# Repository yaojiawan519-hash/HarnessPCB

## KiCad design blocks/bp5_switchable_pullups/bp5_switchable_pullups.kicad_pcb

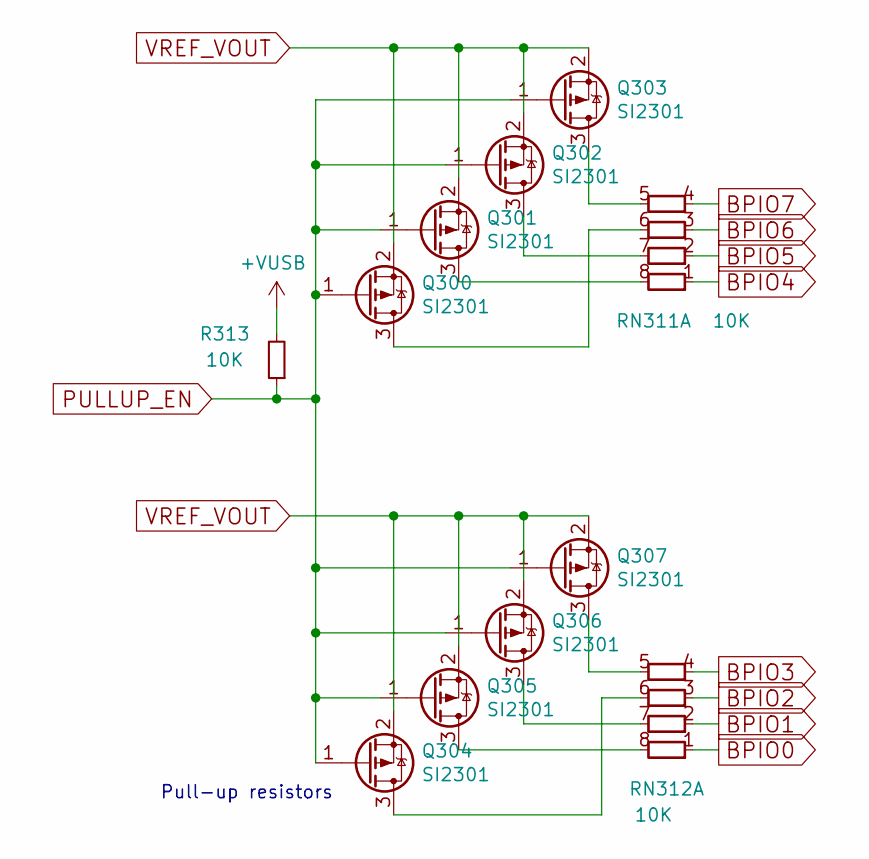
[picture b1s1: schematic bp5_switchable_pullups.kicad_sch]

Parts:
Q300, Q301, Q302, Q303, Q304, Q305, Q306, Q307: SI2301; SOT-523
R313: 10K; R_0402_1005Metric
RN311, RN312: 10K; R_Array_Convex_4x0402

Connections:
+VUSB: R313.2
BPIO0: RN312.1 (R1.1)
BPIO1: RN312.2 (R1.1)
BPIO2: RN312.3 (R1.1)
BPIO3: RN312.4 (R1.1)
BPIO4: RN311.1 (R1.1)
BPIO5: RN311.2 (R1.1)
BPIO6: RN311.3 (R1.1)
BPIO7: RN311.4 (R1.1)
unnamed: Q300.3 (D), RN311.6 (R1.8)
unnamed: Q301.3 (D), RN311.8 (R1.8)
unnamed: Q302.3 (D), RN311.7 (R1.8)
unnamed: Q303.3 (D), RN311.5 (R1.8)
unnamed: Q304.3 (D), RN312.6 (R1.8)
unnamed: Q305.3 (D), RN312.8 (R1.8)
unnamed: Q306.3 (D), RN312.7 (R1.8)
unnamed: Q307.3 (D), RN312.5 (R1.8)
PULLUP_EN: Q300.1 (G), Q301.1 (G), Q302.1 (G), Q303.1 (G), Q304.1 (G), Q305.1 (G), Q306.1 (G), Q307.1 (G), R313.1
VREF_VOUT: Q300.2 (S), Q301.2 (S), Q302.2 (S), Q303.2 (S), Q304.2 (S), Q305.2 (S), Q306.2 (S), Q307.2 (S)

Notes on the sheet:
Pull-up resistors

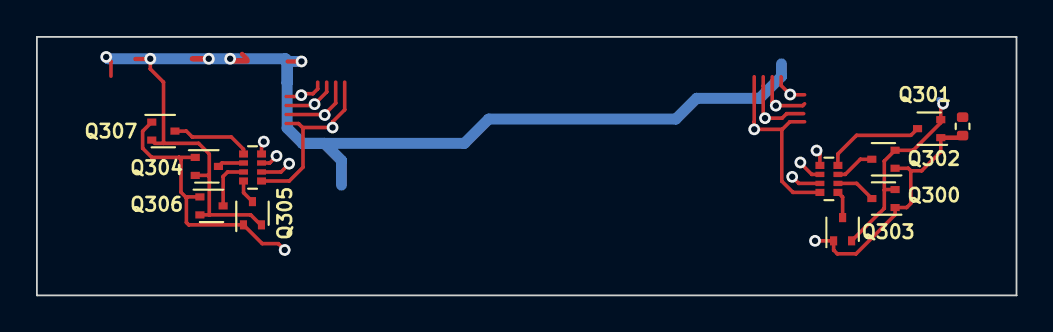
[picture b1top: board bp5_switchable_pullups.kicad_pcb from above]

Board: 4 copper layers, 54.4 x 14.4 mm, 11 parts (0 on the bottom side), 10 nets.

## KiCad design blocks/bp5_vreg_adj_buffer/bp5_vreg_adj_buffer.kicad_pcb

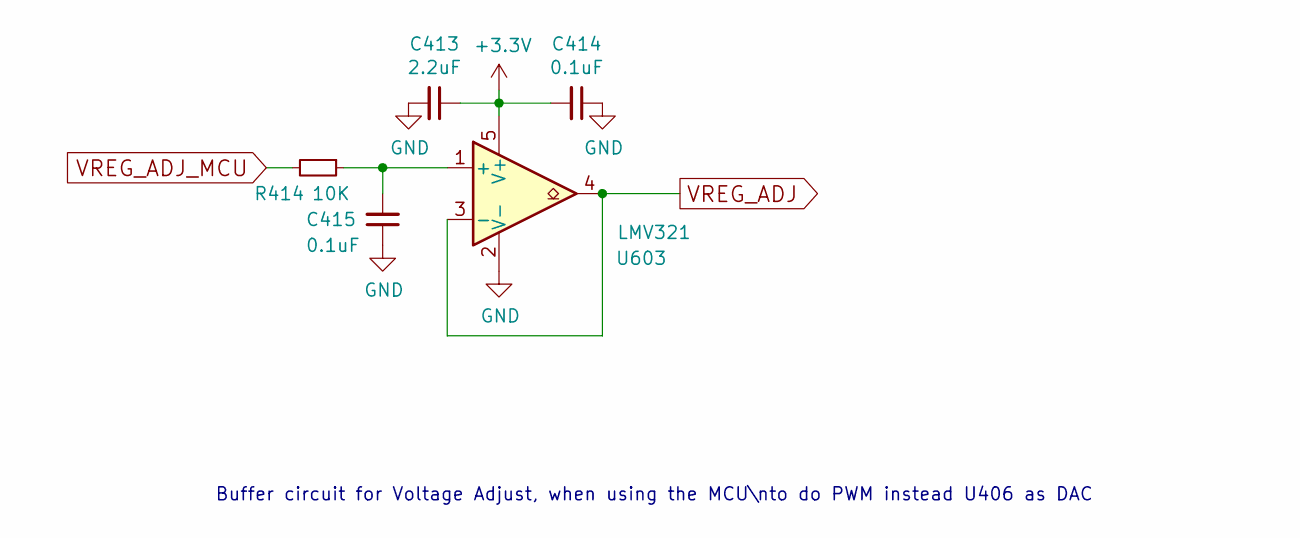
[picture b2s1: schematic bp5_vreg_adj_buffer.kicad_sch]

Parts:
C413: 2.2uF; C_0402_1005Metric
C414, C415: 0.1uF; C_0402_1005Metric
R414: 10K; R_0402_1005Metric
U603: LMV321; SOT-23-5

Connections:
+3V3: C413.1, C414.2, U603.5 (V+)
GND: C413.2, C414.1, C415.1, U603.2 (V-)
unnamed: C415.2, R414.1, U603.1 (+)
VREG_ADJ: U603.3 (-), U603.4
VREG_ADJ_MCU: R414.2

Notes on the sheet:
Buffer circuit for Voltage Adjust, when using the MCU\nto do PWM instead U406 as DAC

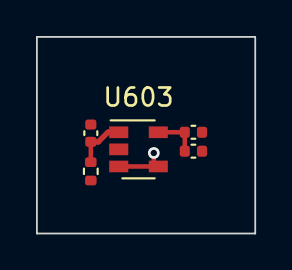
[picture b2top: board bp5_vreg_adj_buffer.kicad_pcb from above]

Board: 4 copper layers, 12.1 x 10.9 mm, 5 parts (0 on the bottom side), 4 nets.

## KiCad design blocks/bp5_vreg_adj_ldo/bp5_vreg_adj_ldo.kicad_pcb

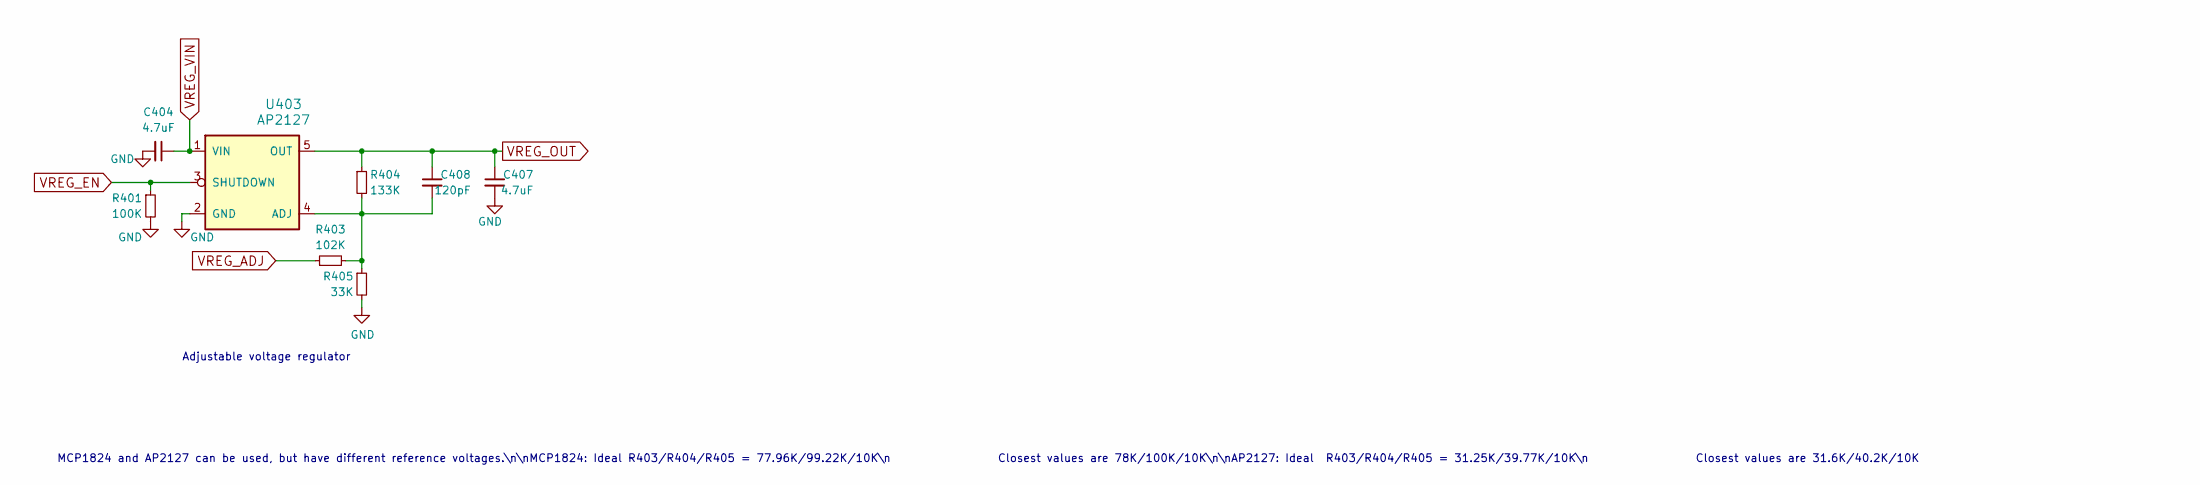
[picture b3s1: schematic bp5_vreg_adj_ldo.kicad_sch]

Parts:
C404, C407: 4.7uF; C_0402_1005Metric
C408: 120pF; C_0402_1005Metric
R401: 100K; R_0402_1005Metric
R403: 102K; R_0402_1005Metric
R404: 133K; R_0402_1005Metric
R405: 33K; R_0402_1005Metric
U403: AP2127; SOT-23-5

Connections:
GND: C404.2, C407.2, R401.2, R405.2, U403.2 (GND)
unnamed: C408.2, R403.2, R404.2, R405.1, U403.4 (ADJ)
VREG_ADJ: R403.1
VREG_EN: R401.1, U403.3 (SHUTDOWN)
VREG_OUT: C407.1, C408.1, R404.1, U403.5 (OUT)
VREG_VIN: C404.1, U403.1 (VIN)

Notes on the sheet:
Adjustable voltage regulator
MCP1824 and AP2127 can be used, but have different reference voltages.\n\nMCP1824: Ideal R403/R404/R405 = 77.96K/99.22K/10K\n Closest values are 78K/100K/10K\n\nAP2127: Ideal R403/R404/R405 = 31.25K/39.77K/10K\n Closest values are 31.6K/40.2K/10K

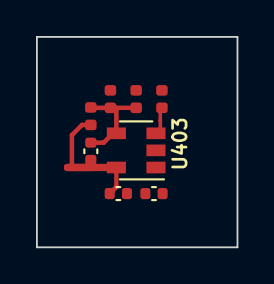
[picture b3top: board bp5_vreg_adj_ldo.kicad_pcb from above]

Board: 4 copper layers, 11.1 x 11.7 mm, 8 parts (0 on the bottom side), 5 nets.

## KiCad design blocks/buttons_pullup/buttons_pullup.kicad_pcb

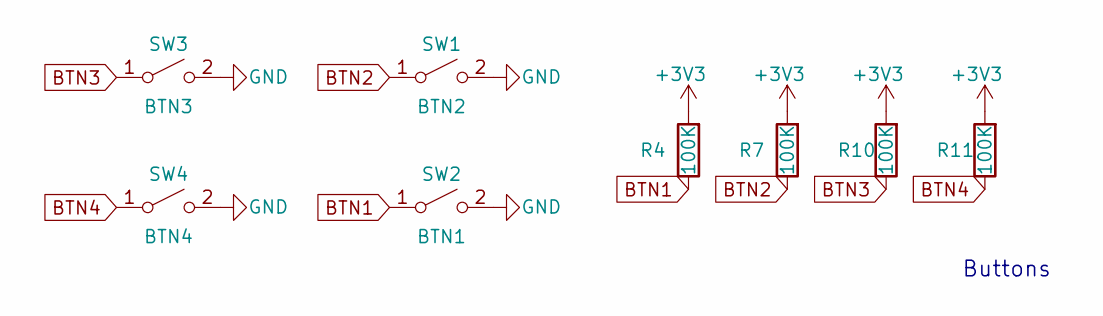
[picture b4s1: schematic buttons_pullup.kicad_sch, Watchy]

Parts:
R4, R7, R10, R11: 100K; R_0402_1005Metric
SW1: BTN2; EVQPUC
SW2: BTN1; EVQPUC
SW3: BTN3; EVQPUC
SW4: BTN4; EVQPUC

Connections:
+3V3: R4.2, R7.2, R10.2, R11.2
BTN1: R4.1, SW2.1 (A)
BTN2: R7.1, SW1.1 (A)
BTN3: R10.1, SW3.1 (A)
BTN4: R11.1, SW4.1 (A)
GND: SW1.2 (B), SW2.2 (B), SW3.2 (B), SW4.2 (B)

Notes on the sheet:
Buttons

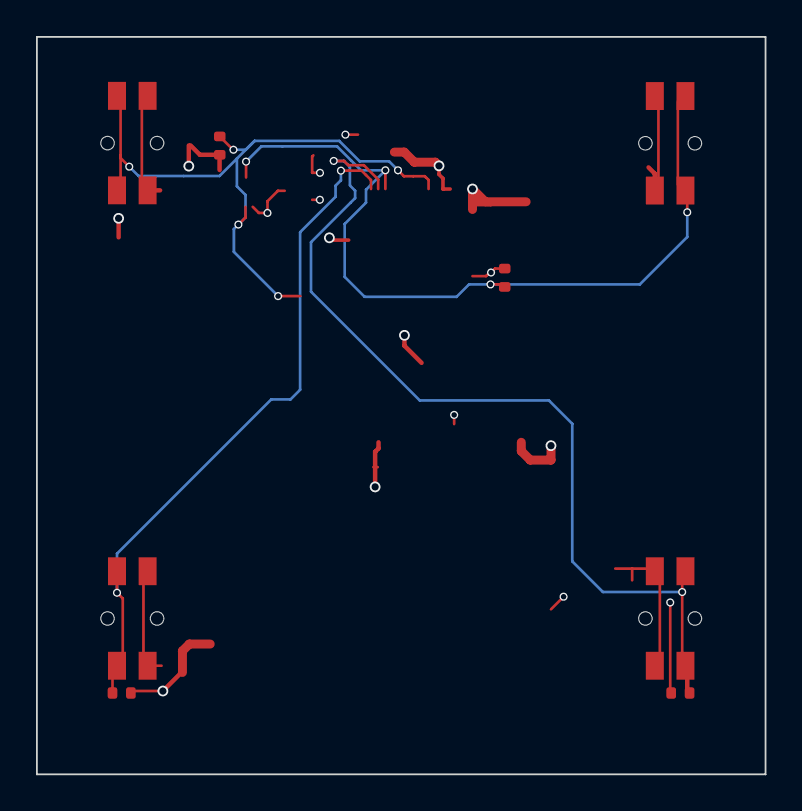
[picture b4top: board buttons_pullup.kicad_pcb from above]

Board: 4 copper layers, 40.5 x 41.0 mm, 8 parts (0 on the bottom side), 6 nets.

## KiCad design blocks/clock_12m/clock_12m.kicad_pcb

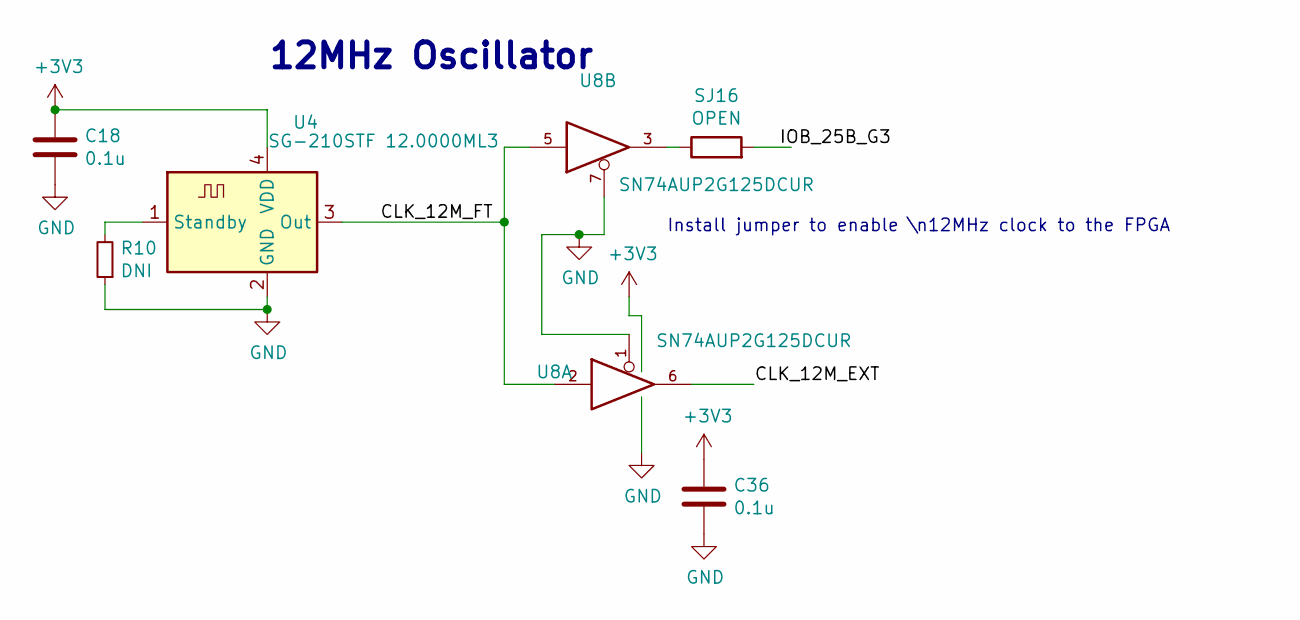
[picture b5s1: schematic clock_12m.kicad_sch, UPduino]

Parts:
C18, C36: 0.1u; C_0603_1608Metric
R10: DNI; R_0603_1608Metric
SJ16: OPEN; SolderJumper-2_0603_Open_TrianglePad1.0x1.5mm
U4: SG-210STF 12.0000ML3; Oscillator_SMD_Abracon_ASDMB-4Pin_2.5x2.0mm
U8: SN74AUP2G125DCUR; VSSOP-8_2.3x2mm_P0.5mm

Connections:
+3V3: C18.1, C36.1, U4.4 (VDD), U8.8 (VCC)
/CLK_12M_EXT: U8.6
/CLK_12M_FT: U4.3 (Out), U8.2, U8.5
/IOB_25B_G3: SJ16.2
GND: C18.2, C36.2, R10.1, U4.2 (GND), U8.1, U8.4 (GND), U8.7
unnamed: R10.2, U4.1 (Standby)
unnamed: SJ16.1, U8.3

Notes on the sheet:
Install jumper to enable \n12MHz clock to the FPGA
12MHz Oscillator

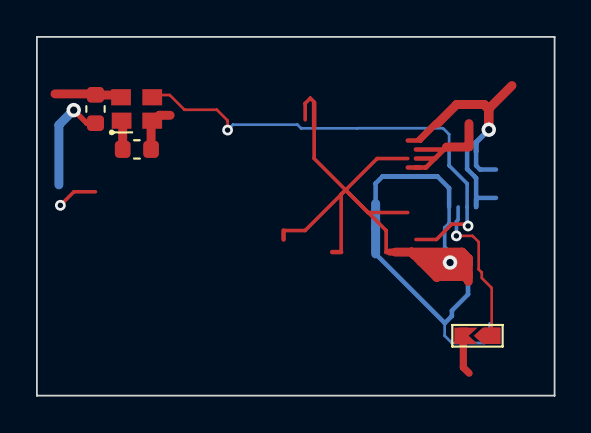
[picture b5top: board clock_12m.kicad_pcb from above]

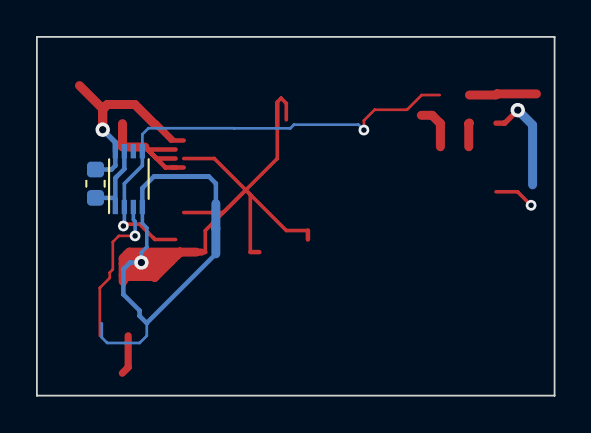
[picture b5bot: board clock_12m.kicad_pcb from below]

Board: 4 copper layers, 28.8 x 19.9 mm, 6 parts (2 on the bottom side), 5 nets.
